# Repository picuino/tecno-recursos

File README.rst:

Tecno Recursos
==============
Web de recursos educativos libres para Tecnología en Educación Secundaria.
Por Carlos Pardo.

`Tecno Recursos. Páginas alojadas en GitHub 
<https://picuino.github.io/es/index.html>`_

`Tecno Recuros. Páginas alojadas en Picuino Web 
<https://www.picuino.com/es/index.html>`_

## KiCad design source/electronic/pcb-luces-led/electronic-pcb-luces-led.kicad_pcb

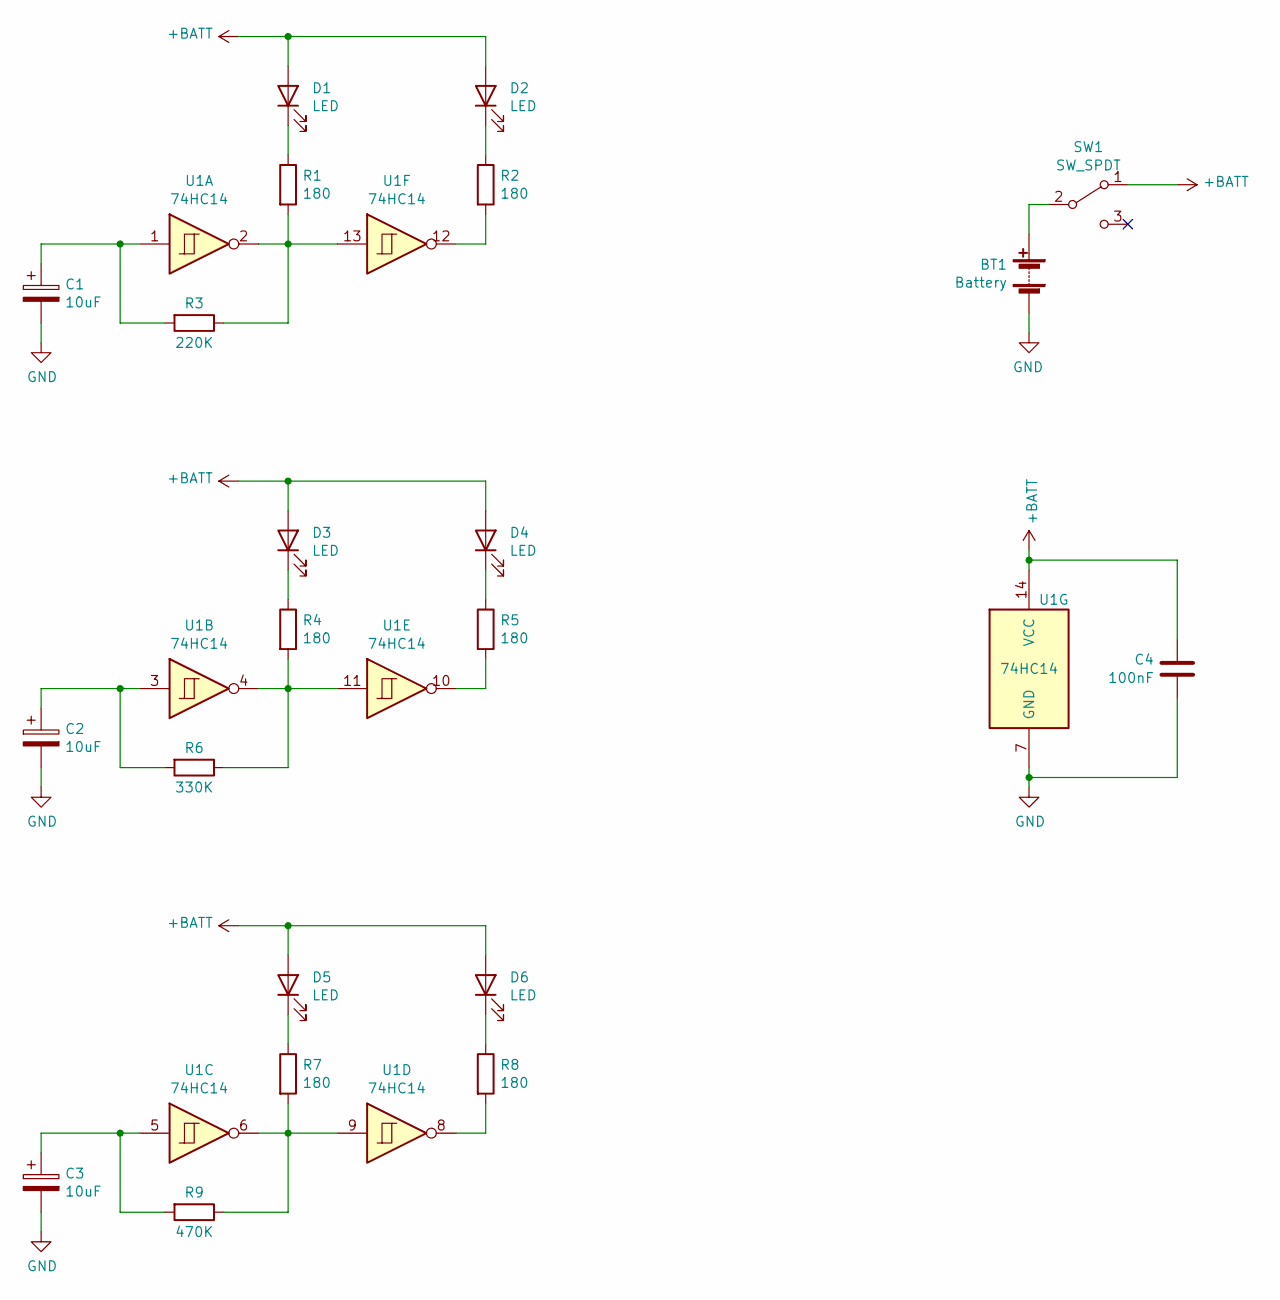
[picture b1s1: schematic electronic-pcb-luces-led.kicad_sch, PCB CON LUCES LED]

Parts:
BT1: Battery; PinHeader_1x02_P2.54mm_Vertical
C1, C2, C3: 10uF; CP_Radial_D5.0mm_P2.00mm
C4: 100nF; C_Rect_L9.0mm_W3.2mm_P7.50mm_MKT
D1, D2, D3, D4, D5, D6: LED; LED_D5.0mm
R1, R2, R4, R5, R7, R8: 180; R_Axial_DIN0411_L9.9mm_D3.6mm_P12.70mm_Horizontal
R3: 220K; R_Axial_DIN0411_L9.9mm_D3.6mm_P12.70mm_Horizontal
R6: 330K; R_Axial_DIN0411_L9.9mm_D3.6mm_P12.70mm_Horizontal
R9: 470K; R_Axial_DIN0411_L9.9mm_D3.6mm_P12.70mm_Horizontal
SW1: SW_SPDT; SW_Slide_1P2T_CK_OS102011MS2Q
U1: 74HC14; DIP-14_W7.62mm_Socket_LongPads

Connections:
+BATT: C4.1, D1.2 (A), D2.2 (A), D3.2 (A), D4.2 (A), D5.2 (A), D6.2 (A), SW1.1 (A), U1.14 (VCC)
GND: BT1.2 (-), C1.2, C2.2, C3.2, C4.2, U1.7 (GND)
unnamed: BT1.1 (+), SW1.2 (B)
unnamed: C1.1, R3.2, U1.1
unnamed: C2.1, R6.2, U1.3
unnamed: C3.1, R9.2, U1.5
unnamed: D1.1 (K), R1.1
unnamed: D2.1 (K), R2.1
unnamed: D3.1 (K), R4.1
unnamed: D4.1 (K), R5.1
unnamed: D5.1 (K), R7.1
unnamed: D6.1 (K), R8.1
unnamed: R1.2, R3.1, U1.2, U1.13
unnamed: R2.2, U1.12
unnamed: R4.2, R6.1, U1.4, U1.11
unnamed: R5.2, U1.10
unnamed: R7.2, R9.1, U1.6, U1.9
unnamed: R8.2, U1.8

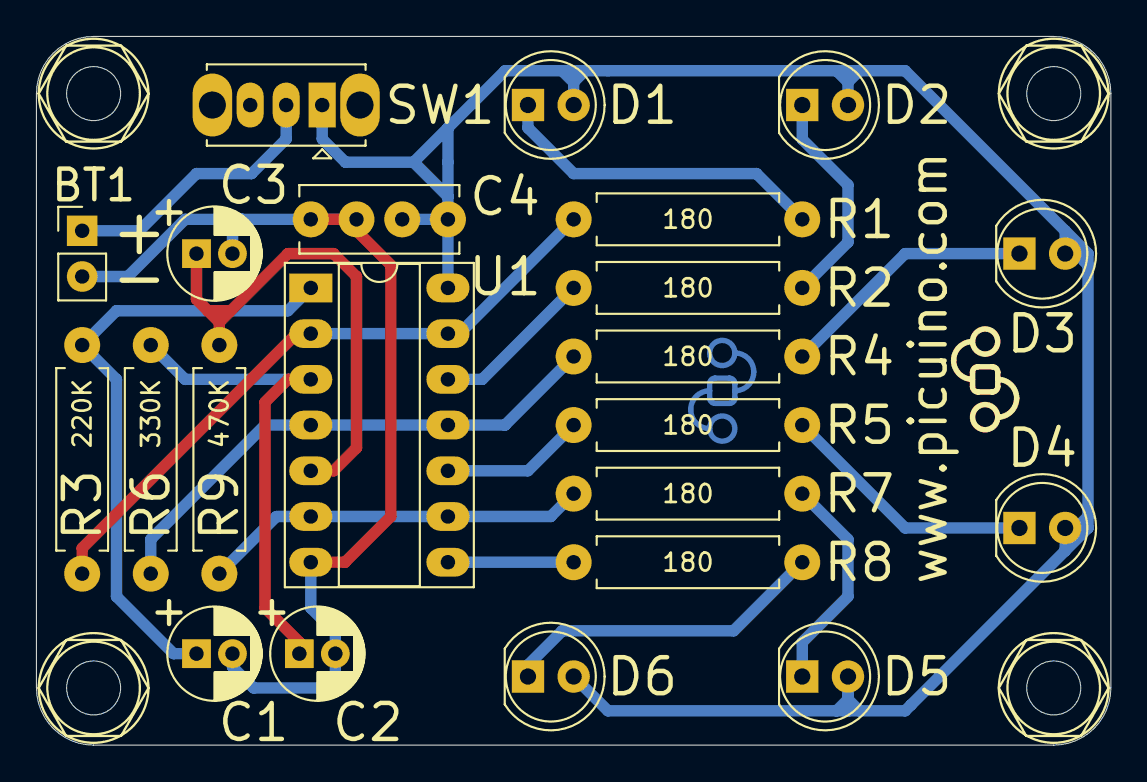
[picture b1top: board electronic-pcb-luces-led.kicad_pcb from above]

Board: 2 copper layers, 59.7 x 39.4 mm, 28 parts (1 on the bottom side), 18 nets.

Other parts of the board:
M3, M3#2, M3#3, M3#4: Val**; SCREW_M3
Picuino_Logo_B6, Picuino_Logo_B6#2: VAL**; Picuino_Logo_B6

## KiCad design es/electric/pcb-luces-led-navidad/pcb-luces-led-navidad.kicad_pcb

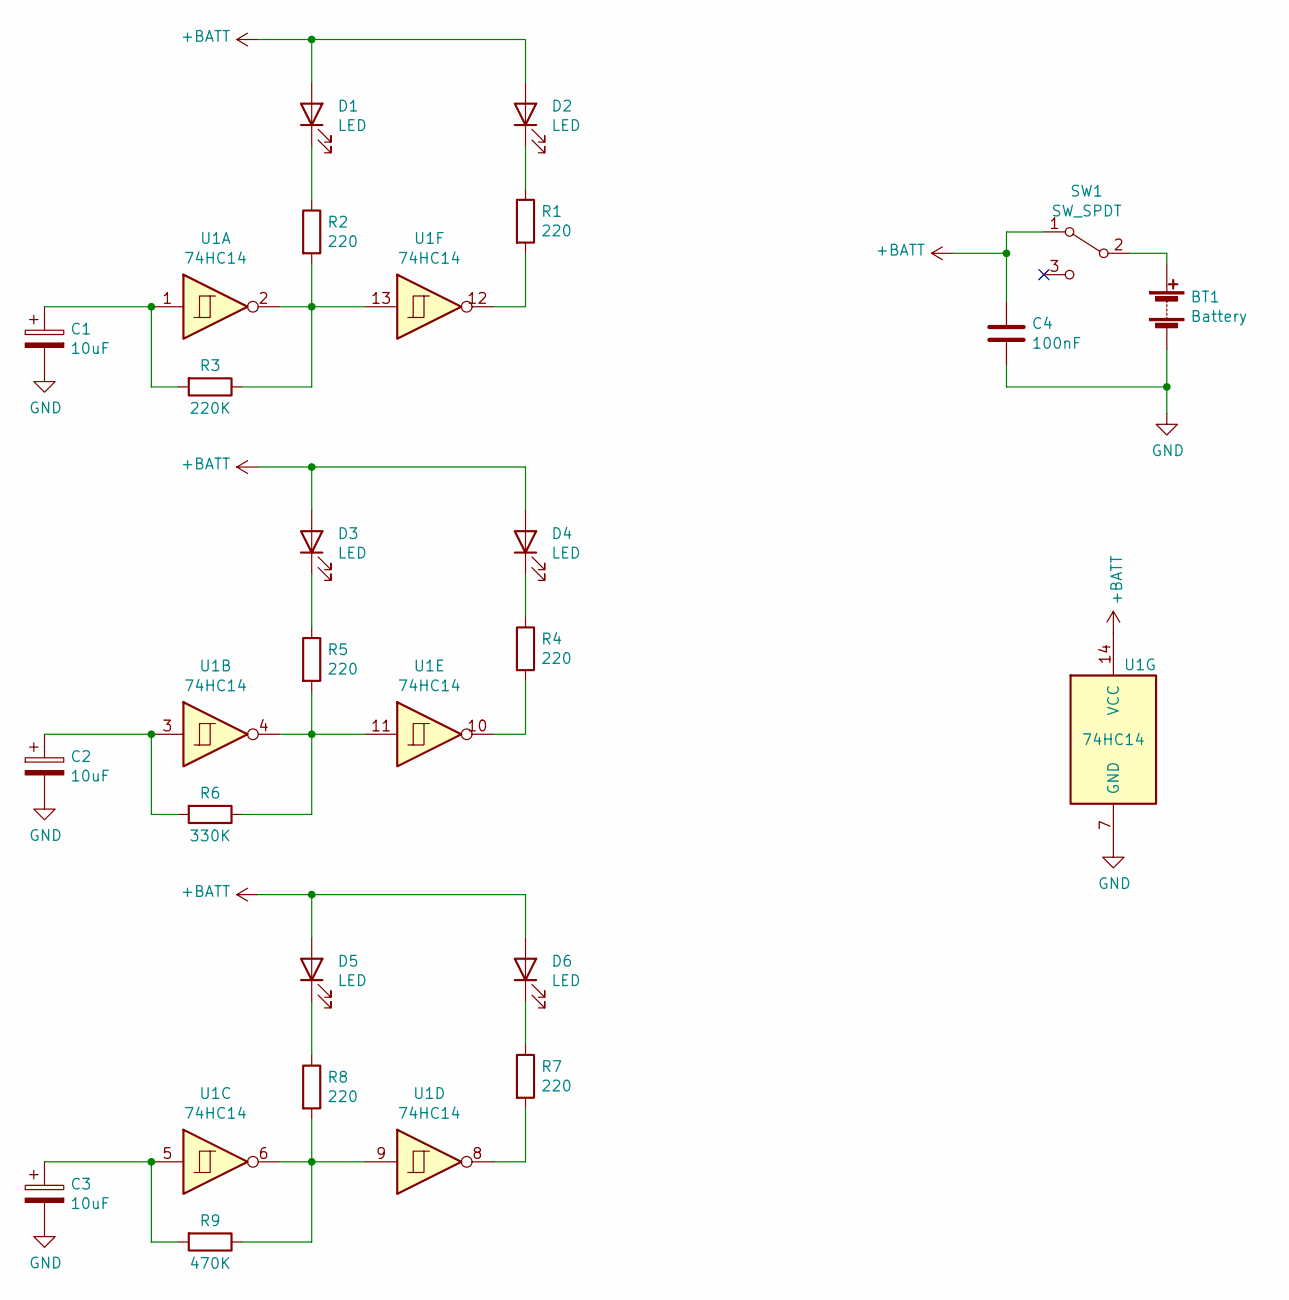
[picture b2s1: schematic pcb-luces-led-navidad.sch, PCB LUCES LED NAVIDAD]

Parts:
BT1: Battery; PinHeader_1x02_P2.54mm_Vertical
C1, C2, C3: 10uF; CP_Radial_D5.0mm_P2.00mm
C4: 100nF; C_Rect_L9.0mm_W3.2mm_P7.50mm_MKT
D1, D2, D3, D4, D5, D6: LED; LED_D5.0mm
R1, R2, R4, R5, R7, R8: 220; R_Axial_DIN0411_L9.9mm_D3.6mm_P12.70mm_Horizontal
R3: 220K; R_Axial_DIN0411_L9.9mm_D3.6mm_P12.70mm_Horizontal
R6: 330K; R_Axial_DIN0411_L9.9mm_D3.6mm_P12.70mm_Horizontal
R9: 470K; R_Axial_DIN0411_L9.9mm_D3.6mm_P12.70mm_Horizontal
SW1: SW_SPDT; SW_Slide_1P2T_CK_OS102011MS2Q
U1: 74HC14; DIP-14_W7.62mm_Socket_LongPads

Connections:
+BATT: C4.1, D1.2 (A), D2.2 (A), D3.2 (A), D4.2 (A), D5.2 (A), D6.2 (A), SW1.1 (A), U1.14 (VCC)
GND: BT1.2 (-), C1.2, C2.2, C3.2, C4.2, U1.7 (GND)
unnamed: BT1.1 (+), SW1.2 (B)
unnamed: C1.1, R3.2, U1.1
unnamed: C2.1, R6.2, U1.3
unnamed: C3.1, R9.2, U1.5
unnamed: D1.1 (K), R2.1
unnamed: D2.1 (K), R1.1
unnamed: D3.1 (K), R5.1
unnamed: D4.1 (K), R4.1
unnamed: D5.1 (K), R8.1
unnamed: D6.1 (K), R7.1
unnamed: R1.2, U1.12
unnamed: R2.2, R3.1, U1.2, U1.13
unnamed: R4.2, U1.10
unnamed: R5.2, R6.1, U1.4, U1.11
unnamed: R7.2, U1.8
unnamed: R8.2, R9.1, U1.6, U1.9

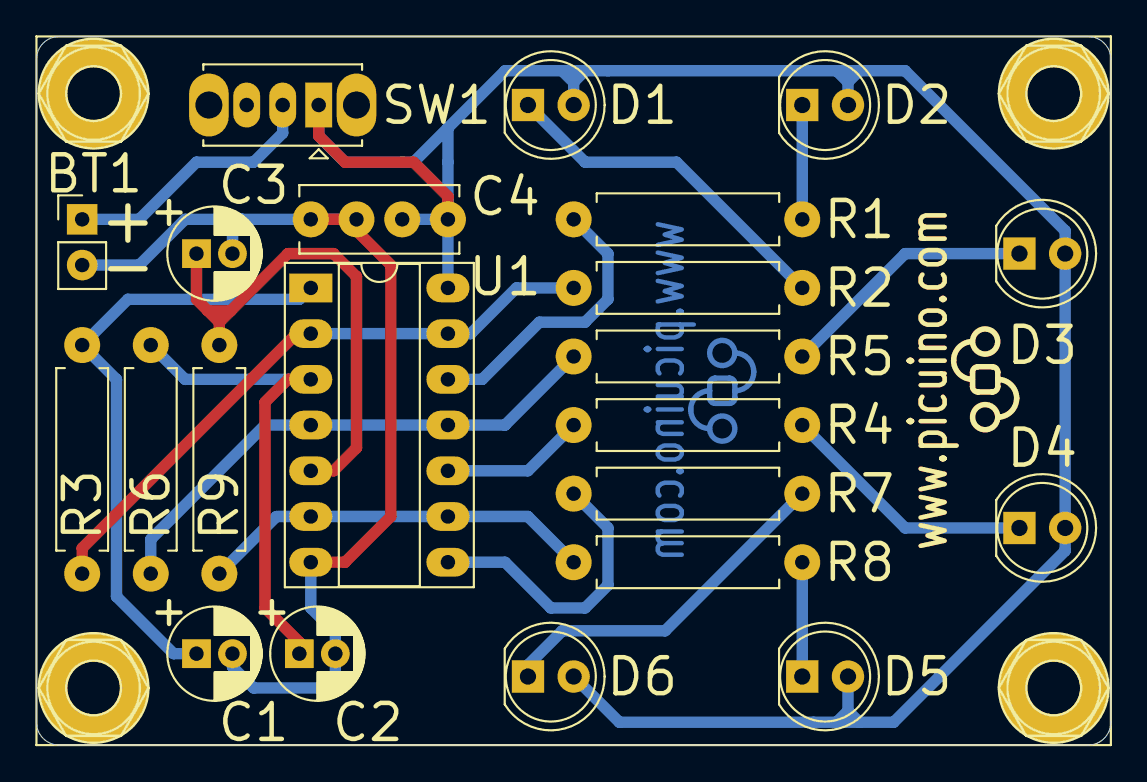
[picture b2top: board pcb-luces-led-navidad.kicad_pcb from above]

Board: 2 copper layers, 59.7 x 39.4 mm, 28 parts (1 on the bottom side), 18 nets.

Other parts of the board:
M3, M3#2, M3#3, M3#4: SCREW_M3
Picuino_Logo_B6, Picuino_Logo_B6#2: VAL**; Picuino_Logo_B6

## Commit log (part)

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2021-07-09 Actualización a 09/07/2021
2021-07-12 Actualización a 12/07/2021
2021-09-12 Libro de tecnología de 4ºESO del CIDEAD
2021-09-12 Cambios de septiembre de 2021
2021-09-12 Libro 4ºESO CIDEAD: Corrección de errores en UD5
2021-09-14 Libro 4ºESO CIDEAD: Añadir simulador ruffle y corrección de errores
2021-09-14 Eliminar del sitemap.xml las páginas web del directorio _static
2021-09-14 Libro 4ºESO CIDEAD: Preguntas UD1 para trabajar
2021-09-15 Libro 4ºESO CIDEAD: Corrección de errores y traducción de videos
2021-09-19 Cambios a 19/09/2021
2021-09-19 Recompresión de imágenes y corrección ortográfica
2021-09-23 Actualización a 23/09/2021. Renderizado de la web.
2021-09-23 charset translated to utf-8
2021-09-26 Optimize
2021-09-26 Añadido Questionary al índice de Picuino
2021-09-26 Rebuild de la web
2021-10-23 Actualizado a 23/10/2021
2021-11-19 Cambios a 19/11/2021
2021-11-25 Cambios 25/11/2021
2021-11-28 Cambios a 28/11/2021
2021-11-28 Rebuild web.
2021-12-04 Cambios a 4/12/2021
2021-12-12 Actualizado a 12/12/2021
2021-12-18 Cambios a 18/12/2021
2021-12-28 Cambios a 28/12/2021
2022-01-05 Luces led Navidad
2022-01-16 Cambios a 16/01/2022
2022-01-20 Cambios a 20/01/2022
2022-01-26 Versión r2
2022-01-26 Cambios a 26/01/2022
2022-01-26 Render web 26/01/2022
2022-01-26 Cambios 26/01/2022
2022-02-09 Actualizado a 09/02/2022
2022-02-22 Cambios a 22/02/2022
2022-03-02 Cambios a 02/03/2022
2022-03-08 Cambios a 08/03/2022
2022-03-13 Cambios a 13/03/2022
2022-03-17 Cambios a 17/03/2022
2022-04-02 Cambios a 02/04/2022
2022-04-15 Cambios a 15/04/2022
2022-05-01 Cambios a 1/05/2022
2022-05-02 Cambios a 2/05/2022
2022-05-08 Cambios a 8/05/2022
2022-05-15 Cambios a 15/05/2022
2022-05-19 Cambios a 19/05/2022
2022-05-19 Cambios a 19/05/2022. Corrección de errores HTML5
2022-05-20 Cambios a 20/05/2022.
2022-05-21 Cambios a 21/05/2022.
2022-05-23 Cambios a 23/05/2022.
2022-05-23 Cambios a 23/05/2022. Actualizar web en GitHub
2022-05-24 Cambios a 24/05/2022. Actualizar web en GitHub
2022-05-25 Cambios a 25/05/2022.
2022-05-28 Cambios a 28/05/2022.
2022-05-29 Cambios a 29/05/2022.
2022-05-30 Cambios a 30/05/2022.
2022-06-02 Cambios a 02/06/2022.
2022-06-04 Cambios a 04/06/2022.
2022-06-04 Trasladar proyectos KiCAD 5 a KiCAD 6. Thickness 12mils
2022-06-06 Cambios a 06/06/2022
2022-06-07 Cambios a 07/06/2022
2022-06-12 Cambios a 12/06/2022
2022-06-16 Cambios a 16/06/2022
2022-06-24 Cambios a 24/06/2022
2022-07-12 Cambios a 12/07/2022
2022-07-20 Cambios a 20/07/2022
2022-08-17 Cambios a 17/08/2022
2022-08-22 Cambios a 22/08/2022
2022-08-23 Cambios a 23/08/2022
2022-08-24 Cambios a 24/08/2022
2022-08-27 Cambios a 27/08/2022
2022-09-01 Cambios a 01/09/2022
2022-09-07 Cambios a 07/09/2022
2022-09-10 Cambios a 10/09/2022
2022-09-28 Cambios a 28/09/2022
2022-10-05 Cambios a 05/10/2022
2022-10-07 Cambios a 07/10/2022
2022-10-08 Cambios a 08/10/2022
2022-10-15 Cambios a 15/10/2022
2022-10-19 Cambios a 19/10/2022
2022-10-21 Cambios a 21/10/2022
2022-10-23 Cambios a 23/10/2022. w3c validator with no errors or warnings.
2022-10-26 Cambios a 26/10/2022. w3c validator with no errors or warnings.
2022-10-29 Cambios a 29/10/2022
2022-11-02 Cambios a 02/11/2022
2022-11-05 Cambios a 05/11/2022
2022-11-06 Cambios a 06/11/2022
2022-11-08 Cambios a 08/11/2022
2022-11-09 Cambios a 09/11/2022
2022-11-10 Cambios a 10/11/2022
2022-11-12 Cambios a 12/11/2022
2022-11-18 Cambios a 18/11/2022
2022-11-19 Cambios a 19/11/2022
2022-11-21 Cambios a 20/11/2022
2022-11-23 Cambios a 23/11/2022
2022-11-27 Cambios a 27/11/2022
2022-11-29 Cambios a 29/11/2022
2022-12-01 Cambios a 01/12/2022
2022-12-02 Cambios a 02/12/2022
2022-12-04 Cambios a 04/12/2022
2022-12-06 Cambios a 06/12/2022
2022-12-17 Cambios a 17/12/2022
2022-12-18 Adding tarfile member sanitization to extractall()
2024-02-14 New commit message after clean project
2024-02-20 20/02/2024 Update
2024-02-21 21/02/2024 Update
2024-02-22 22/02/2024 Update
2024-02-24 24/02/2024 Update
2024-03-05 05/03/2024 Update
2024-03-06 06/03/2024 Update
2024-03-16 16/03/2024 Update
2024-03-23 23/03/2024 Update
2024-04-03 03/04/2024 Update
2024-04-10 10/04/2024 Update
2024-04-11 11/04/2024 Update
2024-04-18 18/04/2024 Update
2024-04-21 21/04/2024 Update
2024-04-25 25/04/2024 Update
2024-05-08 08/05/2024 Update
2024-05-26 26/05/2024 Update
2024-05-31 31/05/2024 Update
2024-06-04 04/06/2024 Update leds -> ledes
2024-06-04 04/06/2024 Update
2024-06-09 09/06/2024 Update
2024-07-05 05/07/2024 Update
2024-08-23 23/08/2024 Update
2024-08-23 23/08/2024 Update LC_MESSAGES
2024-09-01 01/09/2024 Update
2024-09-02 02/09/2024 Update
2024-09-15 15/09/2024 Update
2024-09-19 19/09/2024 Update
2024-09-21 21/09/2024 Update
2024-09-23 23/09/2024 Update
2024-09-24 24/09/2024 Update
2024-09-28 28/09/2024 Update
2024-10-02 02/10/2024 Update
2024-10-04 04/10/2024 Update
2024-10-12 12/10/2024 Update
2024-10-13 13/10/2024 Update
2024-10-15 15/10/2024 Update
2024-10-19 19/10/2024 Update
2024-10-20 20/10/2024 Update
2024-10-21 21/10/2024 Update
2024-10-27 27/10/2024 Update
2024-10-28 28/10/2024 Update
2024-10-31 31/10/2024 Update
2024-11-02 02/11/2024 Update
2024-11-03 03/11/2024 Update
2024-11-06 06/11/2024 Update
2024-11-07 07/11/2024 Update
2024-11-13 13/11/2024 Update
2024-11-14 14/11/2024 Update
2024-11-17 17/11/2024 Update
2024-11-18 18/11/2024 Update
2024-11-21 21/11/2024 Update
2024-11-30 30/11/2024 Update
2024-12-07 07/12/2024 Update
2024-12-10 10/12/2024 Update
2024-12-11 11/12/2024 Update
2024-12-18 18/12/2024 Update
2025-01-04 04/01/2025 Update
2025-01-07 07/01/2025 Update
2025-01-09 09/01/2025 Update
2025-01-09 Remove Docs
2025-01-13 13/01/2025 Update
2025-01-14 14/01/2025 Update
2025-01-15 15/01/2025 Update
2025-01-16 16/01/2025 Update
2025-01-22 22/01/2025 Update
2025-01-25 25/01/2025 Update
2025-01-27 26/01/2025 Update
2025-01-28 28/01/2025 Update
2025-01-29 29/01/2025 Update
2025-02-03 03/02/2025 Update
2025-02-04 04/02/2025 Update
2025-02-11 11/02/2025 Update
2025-02-12 12/02/2025 Update
2025-02-13 13/02/2025 Update
2025-02-18 18/02/2025 Update
2025-02-20 20/02/2025 Update
2025-02-26 26/02/2025 Update
2025-03-02 02/03/2025 Update
2025-03-12 12/03/2025 Update
2025-03-16 16/03/2025 Update
2025-03-17 17/03/2025 Update
2025-03-18 18/03/2025 Update
2025-03-20 20/03/2025 Update
2025-03-25 25/03/2025 Update
2025-04-26 26/04/2025 Update
2025-04-27 27/04/2025 Update
2025-04-30 30/04/2025 Update
2025-05-08 08/05/2025 Update
2025-05-11 11/05/2025 Update
2025-05-12 12/05/2025 Update
2025-05-13 13/05/2025 Update
2025-05-14 14/05/2025 Update
2025-05-21 21/05/2025 Update
2025-05-23 23/05/2025 Update
2025-05-26 26/05/2025 Update
2025-05-27 27/05/2025 Update
2025-06-04 04/06/2025 Update
2025-06-05 05/06/2025 Update
2025-06-09 09/06/2025 Update
2025-06-11 11/06/2025 Update
2025-06-17 17/06/2025 Update
2025-06-21 21/06/2025 Update
2025-06-22 22/06/2025 Update
2025-06-25 25/06/2025 Update
2025-06-26 26/06/2025 Update
2025-06-28 28/06/2025 Update
2025-07-01 01/07/2025 Update
2025-07-02 02/07/2025 Update
2025-07-11 11/07/2025 Update
2025-07-14 14/07/2025 Update
2025-07-15 15/07/2025 Update
2025-07-16 16/07/2025 Update
2025-07-17 17/07/2025 Update
2025-07-21 21/07/2025 Update
2025-07-22 22/07/2025 Update
2025-07-23 23/07/2025 Update
2025-07-24 24/07/2025 Update
2025-07-28 28/07/2025 Update
2025-08-31 31/08/2025 Update
2025-09-02 02/09/2025 Update
2025-09-06 06/09/2025 Update
2025-09-09 09/09/2025 Update
2025-09-10 10/09/2025 Update
2025-09-13 13/09/2025 Update
2025-09-14 14/09/2025 Update
2025-09-19 19/09/2025 Update
2025-09-20 20/09/2025 Update
2025-10-01 01/10/2025 Update
2025-10-03 03/10/2025 Update
2025-10-04 04/10/2025 Update
2025-10-05 05/10/2025 Update
2025-10-15 15/10/2025 Update
2025-10-29 29/10/2025 Update
2025-11-03 03/11/2025 Update
2025-11-10 10/11/2025 Update
2025-11-29 29/11/2025 Update
2025-11-30 30/11/2025 Update
2025-12-11 11/12/2025 Update
2025-12-12 12/12/2025 Update
2025-12-30 30/12/2025 Update
2025-12-31 31/12/2025 Update
2026-01-02 02/01/2026 Update
2026-01-03 03/01/2026 Update
2026-01-04 04/01/2026 Update
2026-01-07 07/01/2026 Update
2026-01-13 13/01/2026 Update
2026-01-15 15/01/2026 Update
2026-01-24 24/01/2026 Update
2026-01-25 25/01/2026 Update
2026-02-03 03/02/2026 Update
2026-02-25 25/02/2026 Update
2026-03-07 07/03/2026 Update
2026-03-08 08/03/2026 Update
2026-03-09 09/03/2026 Update
2026-03-17 17/03/2026 Update
2026-03-22 22/03/2026 Update
2026-03-30 30/03/2026 Update
2026-03-31 31/03/2026 Update
2026-04-02 02/04/2026 Update
2026-04-14 14/04/2026 Update
2026-04-16 16/04/2026 Update
2026-04-20 20/04/2026 Update
2026-04-21 21/04/2026 Update
2026-04-24 24/04/2026 Update
2026-04-24 25/04/2026 Update
2026-04-26 26/04/2026 Update
2026-04-27 27/04/2026 Update
2026-04-28 28/04/2026 Update
2026-04-30 30/04/2026 Update
2026-05-04 04/05/2026 Update
2026-05-06 06/05/2026 Update
2026-05-07 07/05/2026 Update
2026-05-14 14/05/2026 Update
2026-05-17 17/05/2026 Update
2026-05-23 23/05/2026 Update
2026-06-06 06/06/2026 Update
2026-06-09 09/06/2026 Update
2026-06-12 12/06/2026 Update
2026-06-14 14/06/2026 Update
2026-06-15 15/06/2026 Update

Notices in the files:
es/electric/pcb-luces-led-navidad/pcb-luces-led-navidad.kicad_pcb:
Licencia Creative Commons Attribution-ShareAlike 4.0 International
